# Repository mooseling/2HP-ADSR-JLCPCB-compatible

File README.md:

# 2HP ADSR (JLCPCB Compatible)

This is a fork of kraakenstuff/ADSR, which is a 2HP ADSR envelope generator based on René Schmitz's Fastest Envelope in the West design.

Trying to fabricate this with JLCPCB, I've been running into problems:
- JLC won't do any SMT's on a chip smaller than 10mm. I suppose I could just double up the PCB with some snappable edge cuts. But the board was so close to 10mm I just bumped it to 10mm.
- The PCB has diodes with a 0603 footprint. I haven't been able to find a compatible diode in the JLC library, so I've swapped them to SOD-123 packages and moved things around to make them fit.

Status: Don't know yet! There's a good chance I've messed something up, I'm a noob.

Word up homies

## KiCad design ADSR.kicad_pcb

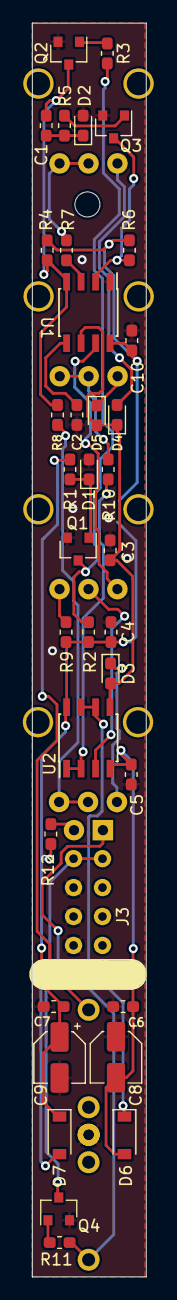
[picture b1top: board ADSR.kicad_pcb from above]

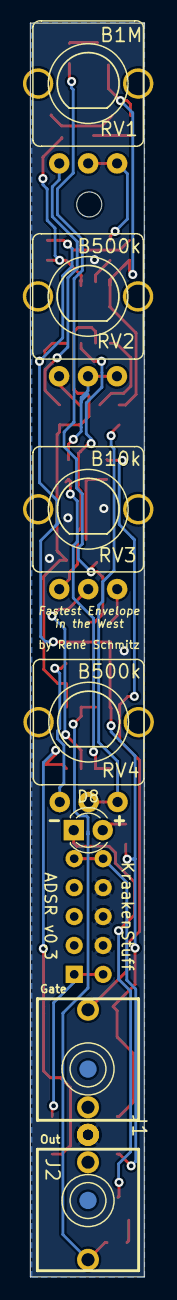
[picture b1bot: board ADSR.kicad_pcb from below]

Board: 2 copper layers, 10.0 x 110.1 mm, 43 parts (7 on the bottom side), 30 nets.

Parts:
C1, C2: 10n; C_0603_1608Metric_Pad1.05x0.95mm_HandSolder
C3: 2.2u; C_0603_1608Metric_Pad1.05x0.95mm_HandSolder
C4, C5, C6, C7, C10: 100n; C_0603_1608Metric_Pad1.05x0.95mm_HandSolder
C8, C9: 10u; CP_Elec_4x4.5
D1, D2, D3, D4, D5: 1n4148; D_0603_1608Metric_Pad1.05x0.95mm_HandSolder
D6, D7: 1N5819; D_SOD-123
D8: LED; LED_D3.0mm
J1: Gate; PJ301M-12-NoHole
J2: Out; PJ301M-12-NoHole
J3: EuroPower; EuroHeader10
Q1, Q2, Q3, Q4: MMBT3904; SOT-23
R1, R5: 10k; R_0603_1608Metric_Pad1.05x0.95mm_HandSolder
R2, R4, R6, R9: 4k7; R_0603_1608Metric_Pad1.05x0.95mm_HandSolder
R3: 22k; R_0603_1608Metric_Pad1.05x0.95mm_HandSolder
R7, R8, R10: 100R; R_0603_1608Metric_Pad1.05x0.95mm_HandSolder
R11: 100k; R_0603_1608Metric_Pad1.05x0.95mm_HandSolder
R12: 1k; R_0603_1608Metric_Pad1.05x0.95mm_HandSolder
RV1: B1M; POT-9MM-ALPHA
RV2, RV4: B500k; POT-9MM-ALPHA
RV3: B10k; POT-9MM-ALPHA
U1: NE555; SOIC-8_3.9x4.9mm_P1.27mm
U2: LM358; SOIC-8_3.9x4.9mm_P1.27mm

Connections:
+12V: C4.2, C7.2, C9.1, C10.1, D7.1, R2.2, R4.2, R6.2, R9.2, R12.1, U1.8, U2.8
-12V: C5.1, C6.1, C8.2, D6.2, U2.4
GND: C2.1, C3.1, C4.1, C5.2, C6.2, C7.1, C8.1, C9.2, C10.2, D1.2, D2.2, J1.S, J2.S, J3.4, J3.6, J3.8, Q1.2, Q2.2, Q3.2, Q4.2, U1.1
unnamed: C1.1, D2.1, R5.2
unnamed: C1.2, Q2.3, R4.1, R8.2, U1.4
unnamed: C2.2, U1.5
unnamed: C3.2, D3.2, D4.1, D5.2, U1.6, U2.5
unnamed: D1.1, Q1.1, R1.1
unnamed: D3.1, RV4.1
unnamed: D4.2, RV1.1
unnamed: D5.1, RV2.1
unnamed: D6.1, J3.2
unnamed: D7.2, J3.10
unnamed: D8.1, Q4.3
unnamed: D8.2, R12.2
unnamed: J1.T, R1.2
unnamed: J2.T, R11.2, U2.6, U2.7
unnamed: Q1.3, R2.1, R3.2
unnamed: Q2.1, R3.1
unnamed: Q3.1, R5.1
unnamed: Q3.3, R6.1, U1.2
unnamed: Q4.1, R11.1
unnamed: R7.1, RV1.2, RV1.3
unnamed: R7.2, U1.3
unnamed: R8.1, RV4.2, RV4.3
unnamed: R9.1, RV3.3
unnamed: R10.1, U2.1, U2.2
unnamed: R10.2, RV2.2, RV2.3
unnamed: RV3.1, U1.7
unnamed: RV3.2, U2.3

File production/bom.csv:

Designator,Footprint,Quantity,Value,LCSC Part #
"C1, C2",0603,2,10n,
"C10, C4, C5, C6, C7",0603,5,100n,
C3,0603,1,2.2u,
"C8, C9",CP_Elec_4x4.5,2,10u,
"D1, D2, D3, D4, D5",D_SOD-123,5,1n4148,
"D6, D7",D_SOD-123,2,1N5819,
D8,LED_D3.0mm,1,LED,
J1,PJ301M-12-NoHole,1,Gate,
J2,PJ301M-12-NoHole,1,Out,
J3,EuroHeader10,1,EuroPower,
"Q1, Q2, Q3, Q4",SOT-23,4,MMBT3904,
"R1, R5",0603,2,10k,
"R10, R7, R8",0603,3,100R,
R11,0603,1,100k,
R12,0603,1,1k,
"R2, R4, R6, R9",0603,4,4k7,
R3,0603,1,22k,
RV1,POT-9MM-ALPHA,1,B1M,
"RV2, RV4",POT-9MM-ALPHA,2,B500k,
RV3,POT-9MM-ALPHA,1,B10k,
U1,SOIC-8_3.9x4.9mm_P1.27mm,1,NE555,
U2,SOIC-8_3.9x4.9mm_P1.27mm,1,LM358,

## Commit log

2024-11-02 gitignore DS_store files
2024-11-02 Make width 10mm, use SOD-123 package diodes
2024-11-02 Use fabrication tools plugin for JLC-targetted outputs
